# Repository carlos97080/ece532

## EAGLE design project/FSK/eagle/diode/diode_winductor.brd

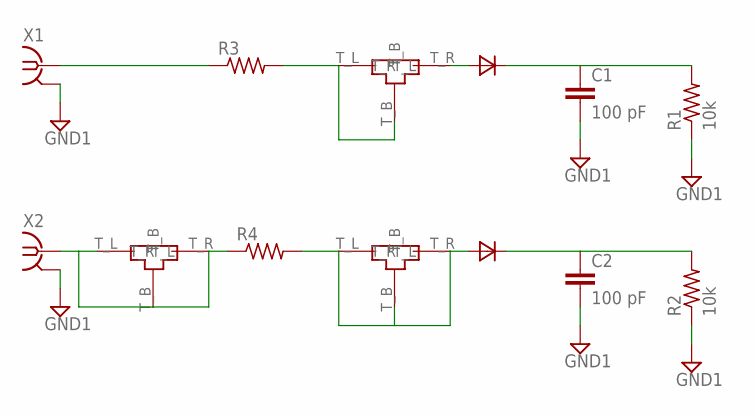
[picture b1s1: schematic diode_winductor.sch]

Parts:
C1, C2: 100 pF; C0603
INPUT, INPUT1, INPUT2: TEE_TL1
R1, R2: 10k; M1206
R3, R4: R-US_R0603; R0603
U$1, U$2: HSMS-2850
X1, X2: SMA-142-0701-801/806; J502-ND-142-0701-801/806

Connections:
GND1: C1.2, C2.2, R1.1, R2.1, X1.G@1 (2), X1.G@2 (2), X1.G@3 (2), X1.G@4 (2), X2.G@1 (2), X2.G@2 (2), X2.G@3 (2), X2.G@4 (2)
INPUT: INPUT.T_B, INPUT.T_L, INPUT.T_R, R3.2, U$1.A
INPUT1: INPUT2.T_B, INPUT2.T_L, INPUT2.T_R, R4.1, X2.1
INPUT2: INPUT1.T_B, INPUT1.T_L, INPUT1.T_R, R4.2, U$2.A
INPUT11: R3.1, X1.1
unnamed: C1.1, R1.2, U$1.C
unnamed: C2.1, R2.2, U$2.C

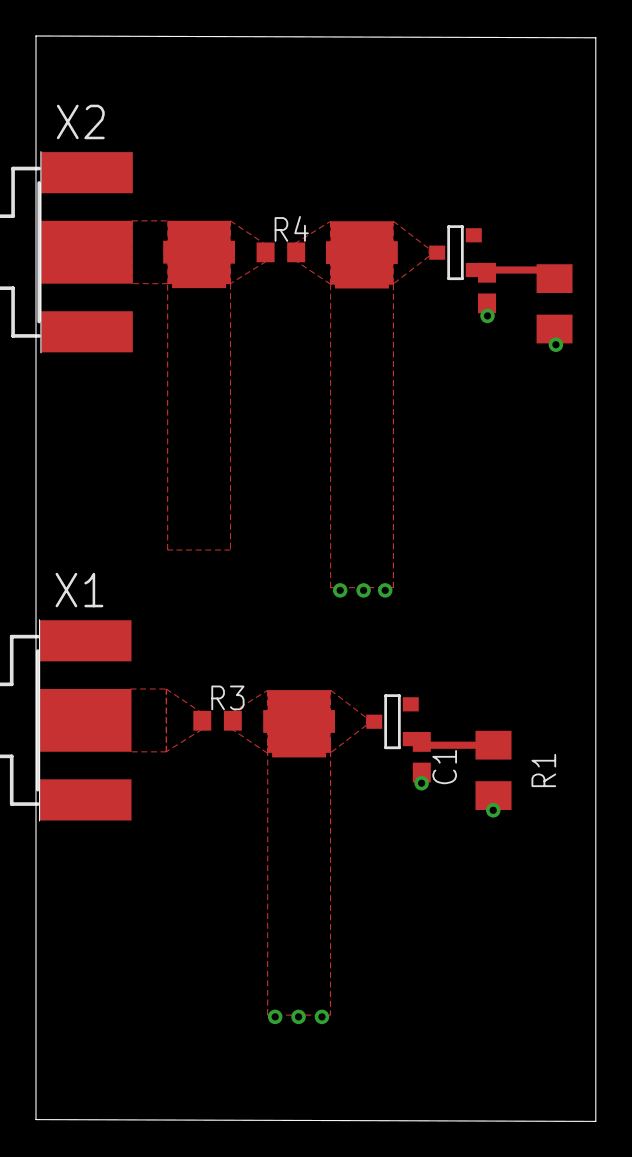
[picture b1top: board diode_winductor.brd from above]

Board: 2 copper layers, 31.1 x 60.3 mm, 13 parts (0 on the bottom side), 7 nets.

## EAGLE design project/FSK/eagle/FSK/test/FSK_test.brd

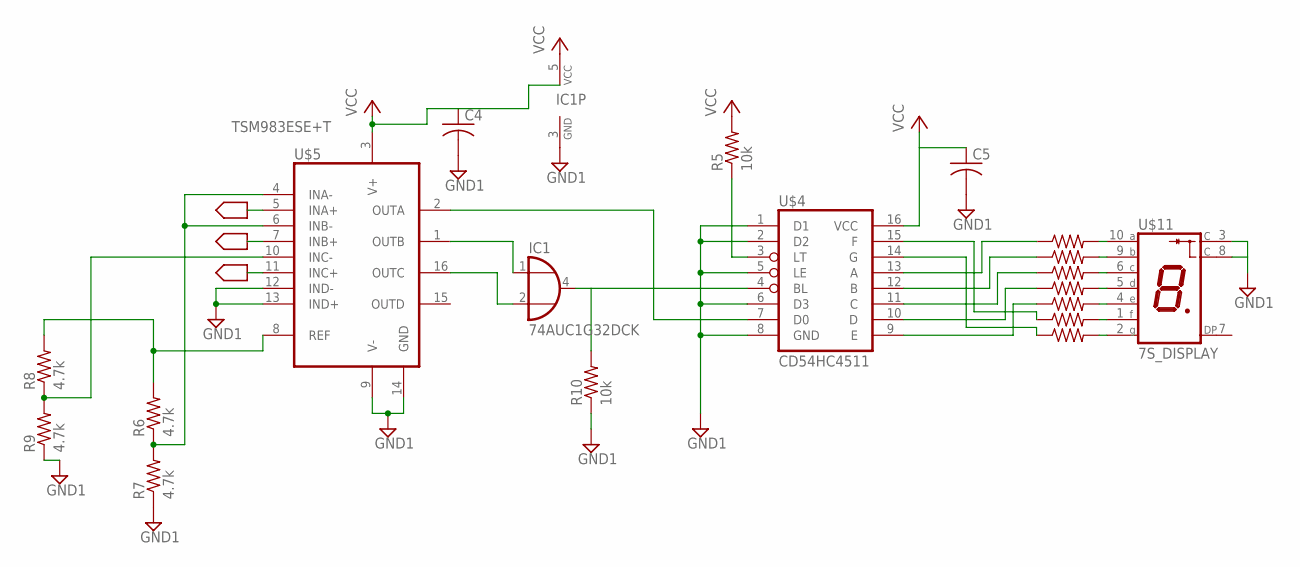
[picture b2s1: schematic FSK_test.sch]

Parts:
C4, C5: C-USC0603; C0603
IC1: 74AUC1G32DCK; SC70-5
R5, R10: 10k; R1206
R6, R7, R8, R9: 4.7k; R1206
R11, R12, R13, R14, R15, R16, R17: R-US_R0603; R0603
U$4: CD54HC4511
U$5: TSM983ESE+T
U$11: 7S_DISPLAY

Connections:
2.4_OUT: U$5.5 (INA+)
2.6_OUT: U$5.7 (INB+), U$5.11 (INC+)
GND1: C4.2, C5.2, IC1.3 (GND), R7.1, R9.1, R10.1, U$4.1 (D1), U$4.2 (D2), U$4.5 (LE), U$4.6 (D3), U$4.8 (GND), U$5.9 (V-), U$5.12 (IND-), U$5.13 (IND+), U$5.14 (GND), U$11.3 (C), U$11.8 (C)
unnamed: IC1.4 (O), R10.2, U$4.4 (BL)
unnamed: IC1.1 (I0), U$5.1 (OUTB)
unnamed: R11.2, U$11.10 (A)
unnamed: R12.2, U$11.9 (B)
unnamed: U$4.7 (D0), U$5.2 (OUTA)
unnamed: R13.2, U$11.6 (C)
unnamed: IC1.2 (I1), U$5.16 (OUTC)
unnamed: R8.1, R9.2, U$5.10 (INC-)
unnamed: R6.2, R8.2, U$5.8 (REF)
unnamed: R6.1, R7.2, U$5.4 (INA-), U$5.6 (INB-)
unnamed: R5.1, U$4.3 (LT)
unnamed: R14.2, U$11.5 (D)
unnamed: R15.2, U$11.4 (E)
unnamed: R16.2, U$11.1 (F)
unnamed: R17.2, U$11.2 (G)
unnamed: R11.1, U$4.13 (A)
unnamed: R12.1, U$4.12 (B)
unnamed: R13.1, U$4.11 (C)
unnamed: R14.1, U$4.10 (D)
unnamed: R15.1, U$4.9 (E)
unnamed: R16.1, U$4.15 (F)
unnamed: R17.1, U$4.14 (G)
VCC: C4.1, C5.1, IC1.5 (VCC), R5.2, U$4.16 (VCC), U$5.3 (V+)

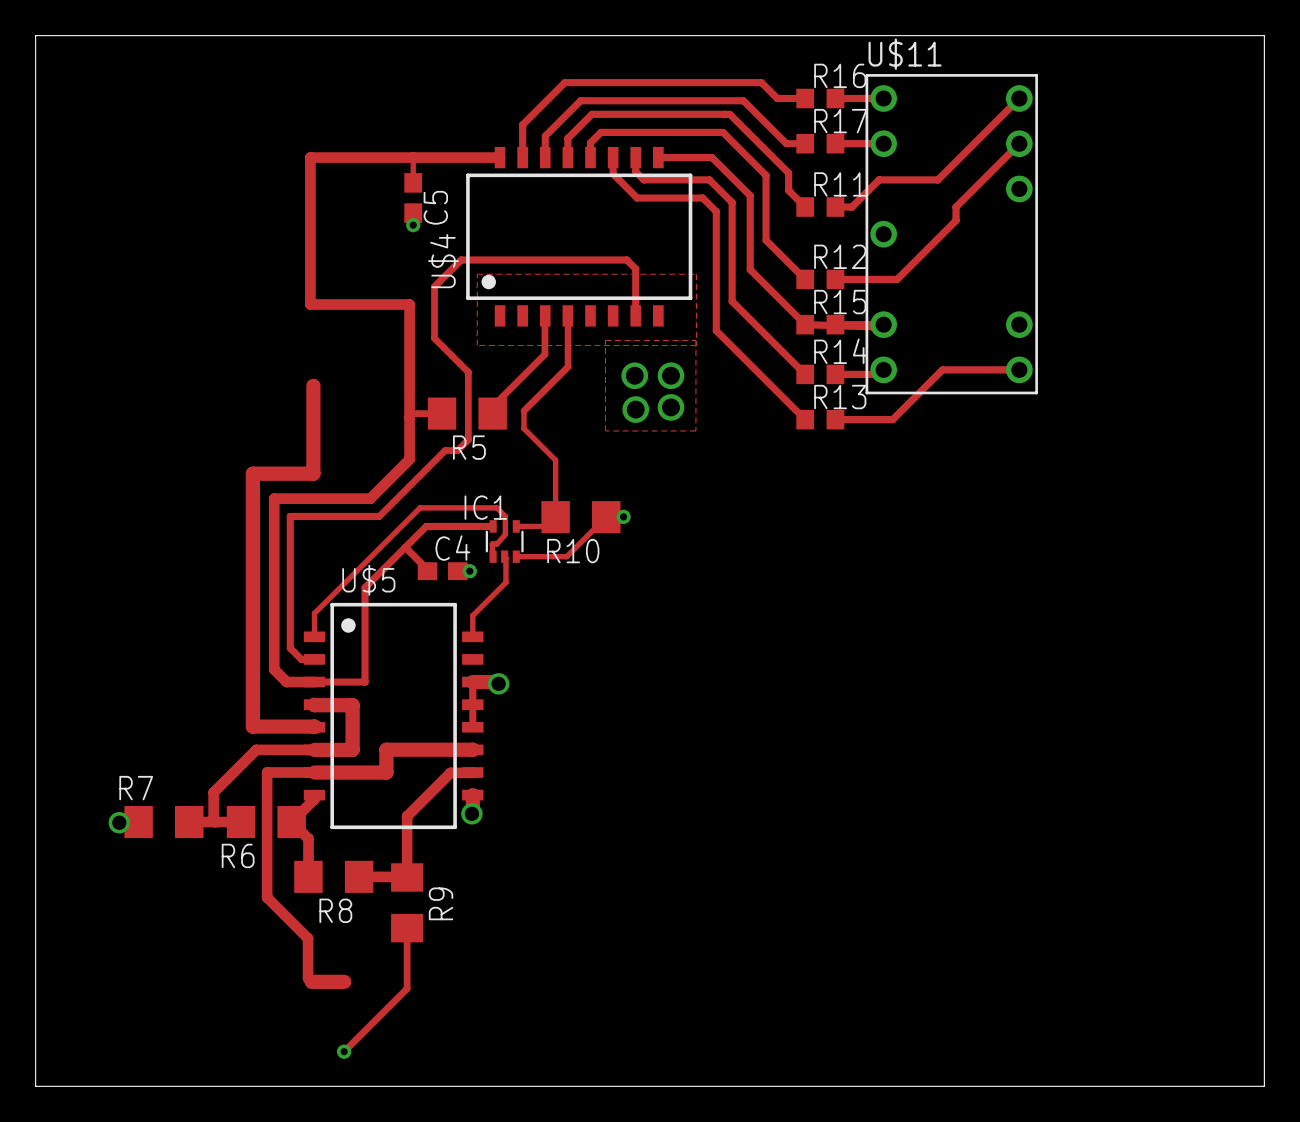
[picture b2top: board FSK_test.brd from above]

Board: 2 copper layers, 69.0 x 59.0 mm, 19 parts (0 on the bottom side), 25 nets.

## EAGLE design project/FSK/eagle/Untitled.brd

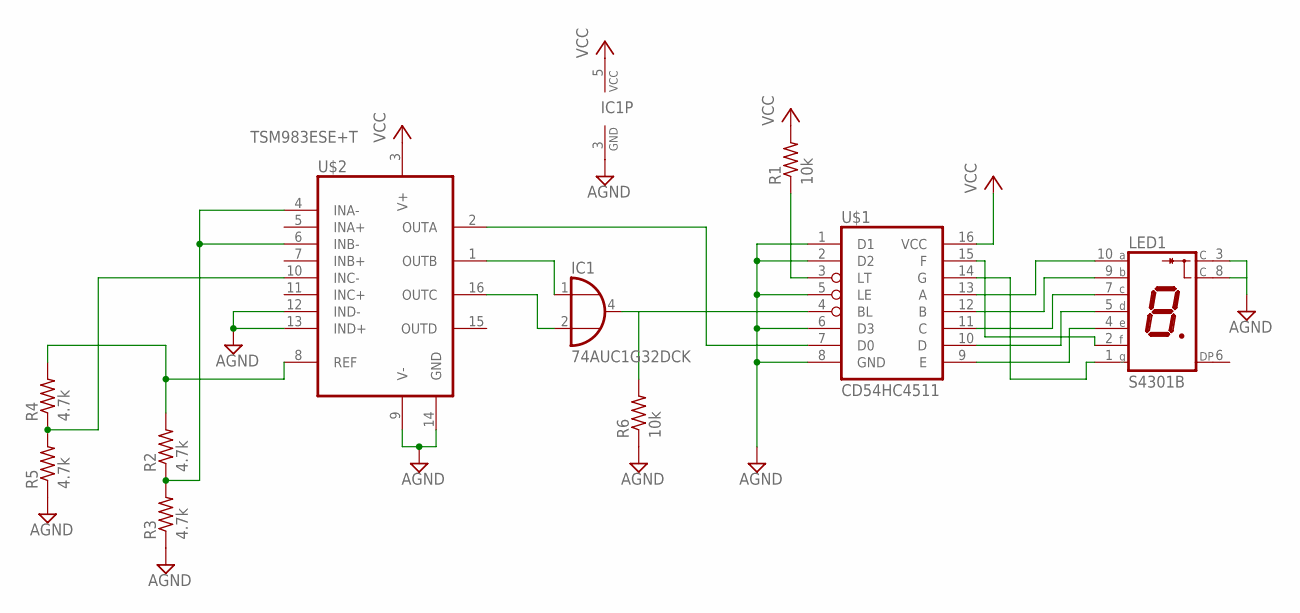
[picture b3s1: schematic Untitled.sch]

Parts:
IC1: 74AUC1G32DCK; SC70-5
LED1: S4301B
R1, R6: 10k; R1206
R2, R3, R4, R5: 4.7k; R1206
U$1: CD54HC4511
U$2: TSM983ESE+T

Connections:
AGND: IC1.3 (GND), LED1.3 (C), LED1.8 (C), R3.1, R5.1, R6.1, U$1.1 (D1), U$1.2 (D2), U$1.5 (LE), U$1.6 (D3), U$1.8 (GND), U$2.9 (V-), U$2.12 (IND-), U$2.13 (IND+), U$2.14 (GND)
unnamed: IC1.1 (I0), U$2.1 (OUTB)
unnamed: R1.1, U$1.3 (LT)
unnamed: IC1.4 (O), R6.2, U$1.4 (BL)
unnamed: IC1.2 (I1), U$2.16 (OUTC)
unnamed: R4.1, R5.2, U$2.10 (INC-)
unnamed: U$1.7 (D0), U$2.2 (OUTA)
unnamed: R2.1, R3.2, U$2.4 (INA-), U$2.6 (INB-)
unnamed: LED1.4 (E), U$1.9 (E)
unnamed: LED1.5 (D), U$1.10 (D)
unnamed: R2.2, R4.2, U$2.8 (REF)
unnamed: LED1.7 (C), U$1.11 (C)
unnamed: LED1.9 (B), U$1.12 (B)
unnamed: LED1.10 (A), U$1.13 (A)
unnamed: LED1.1 (G), U$1.14 (G)
unnamed: LED1.2 (F), U$1.15 (F)
VCC: IC1.5 (VCC), R1.2, U$1.16 (VCC), U$2.3 (V+)

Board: 2 copper layers, 10 parts (0 on the bottom side), 17 nets, no tracks yet.

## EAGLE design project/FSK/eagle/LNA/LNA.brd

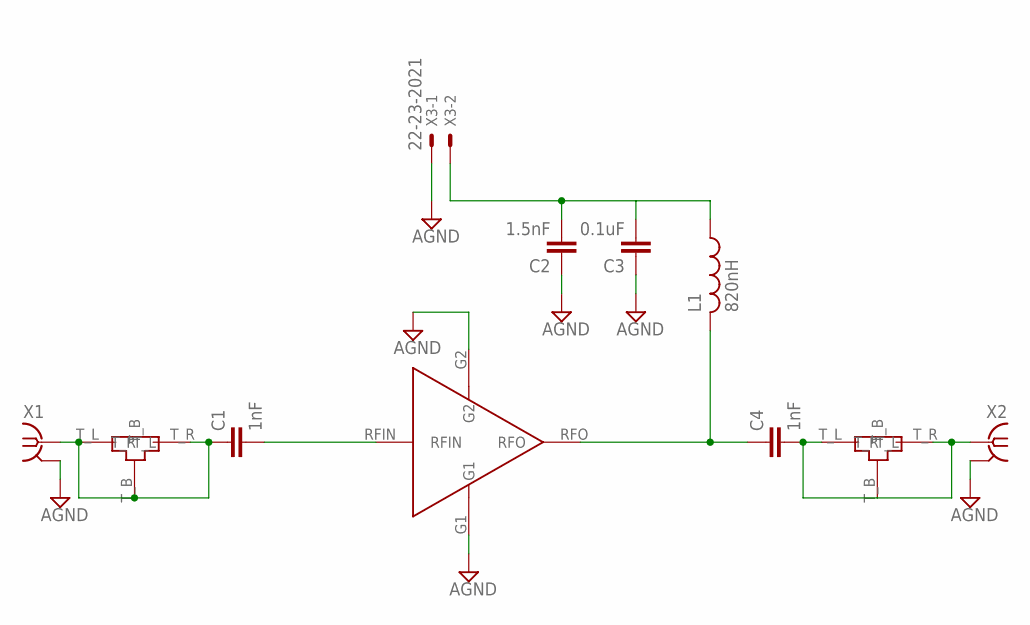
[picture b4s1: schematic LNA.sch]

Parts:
C1, C4: 1nF; C0603
C2: 1.5nF; C0603
C3: 0.1uF; C0603
IN1: TEE_TL1
L1: 820nH; L3230M
OUT2: TEE_TL1
U$1: PSA4-5043+
X1, X2: SMA-142-0711-821/826; J502-ND-142-0711-821/826
X3: 22-23-2021

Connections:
AGND: C2.1, C3.1, U$1.G1, U$1.G2, X1.G@1 (2), X1.G@2 (2), X1.G@3 (2), X1.G@4 (2), X2.G@1 (2), X2.G@2 (2), X2.G@3 (2), X2.G@4 (2), X3.1
EIP: C2.2, C3.2, L1.1, X3.2
IN: C1.2, U$1.RFIN
IN1: C1.1, IN1.T_B, IN1.T_L, IN1.T_R, X1.1
OUT: C4.1, L1.2, U$1.RFO
OUT2: C4.2, OUT2.T_B, OUT2.T_L, OUT2.T_R, X2.1

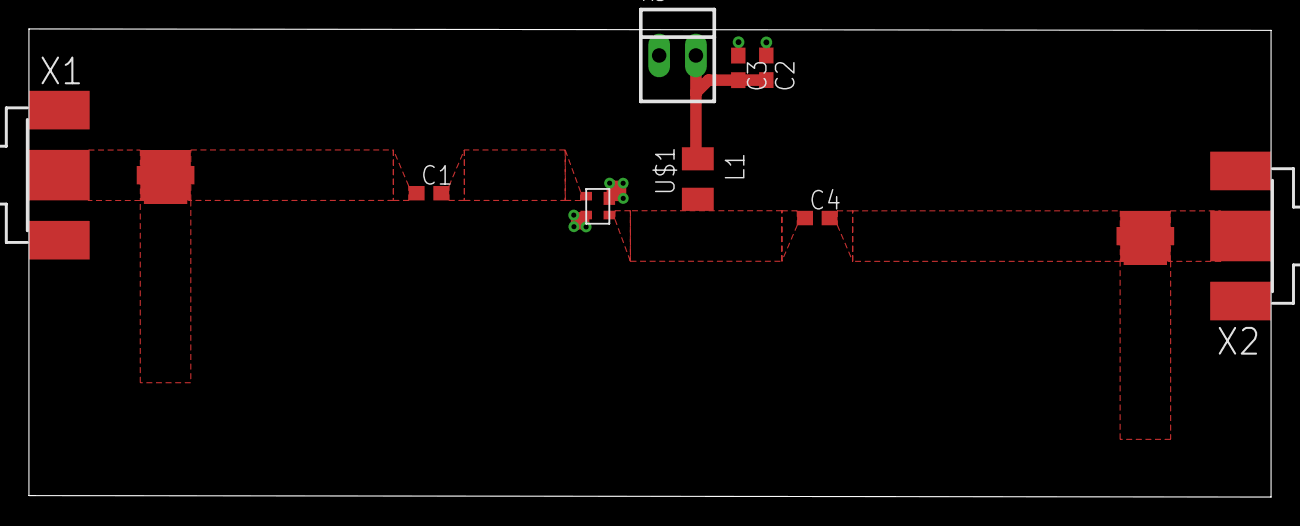
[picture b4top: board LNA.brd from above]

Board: 2 copper layers, 85.8 x 32.4 mm, 11 parts (0 on the bottom side), 6 nets.

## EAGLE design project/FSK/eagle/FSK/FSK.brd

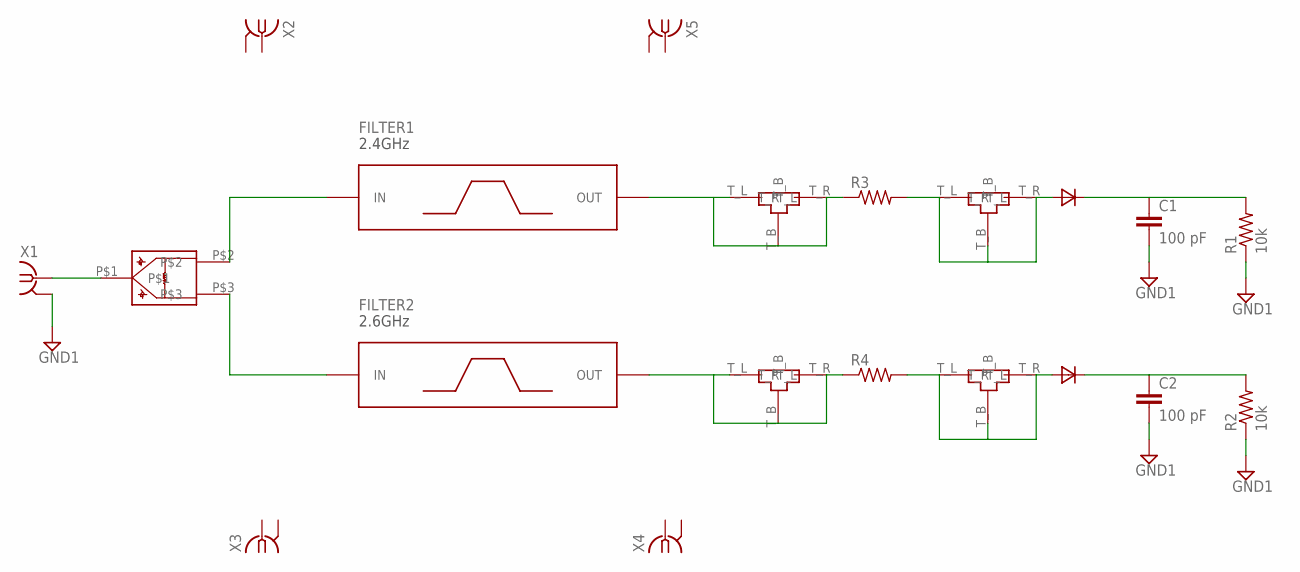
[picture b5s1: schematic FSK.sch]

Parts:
2.4FIL, 2.4TUNED, 2.6FIL, 2.6TUNED: TEE_TL1
C1, C2: 100 pF; C0603
FILTER1: 2.4GHz; 1IN_PIPE_CAP
FILTER2: 2.6GHz; 1IN_PIPE_CAP
R1, R2: 10k; M1206
R3, R4: R-US_R0603; R0603
U$1: WSPLITTER_2.5GHZ
U$2, U$3: HSMS-2850
X1, X2, X3, X4, X5: SMA-142-0711-821/826; J502-ND-142-0711-821/826

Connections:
2.4FIL: 2.4FIL.T_B, 2.4FIL.T_L, 2.4FIL.T_R, FILTER1.OUT, R3.1
2.4GHZ: FILTER1.IN, U$1.P$2
2.4TUNED: 2.4TUNED.T_B, 2.4TUNED.T_L, 2.4TUNED.T_R, R3.2, U$2.A
2.6FIL: 2.6FIL.T_B, 2.6FIL.T_L, 2.6FIL.T_R, FILTER2.OUT, R4.1
2.6GHZ: FILTER2.IN, U$1.P$3
2.6TUNED: 2.6TUNED.T_B, 2.6TUNED.T_L, 2.6TUNED.T_R, R4.2, U$3.A
GND1: C1.2, C2.2, R1.1, R2.1, X1.G@1 (2), X1.G@2 (2), X1.G@3 (2), X1.G@4 (2)
unnamed: C1.1, R1.2, U$2.C
unnamed: C2.1, R2.2, U$3.C
unnamed: U$1.P$1, X1.1

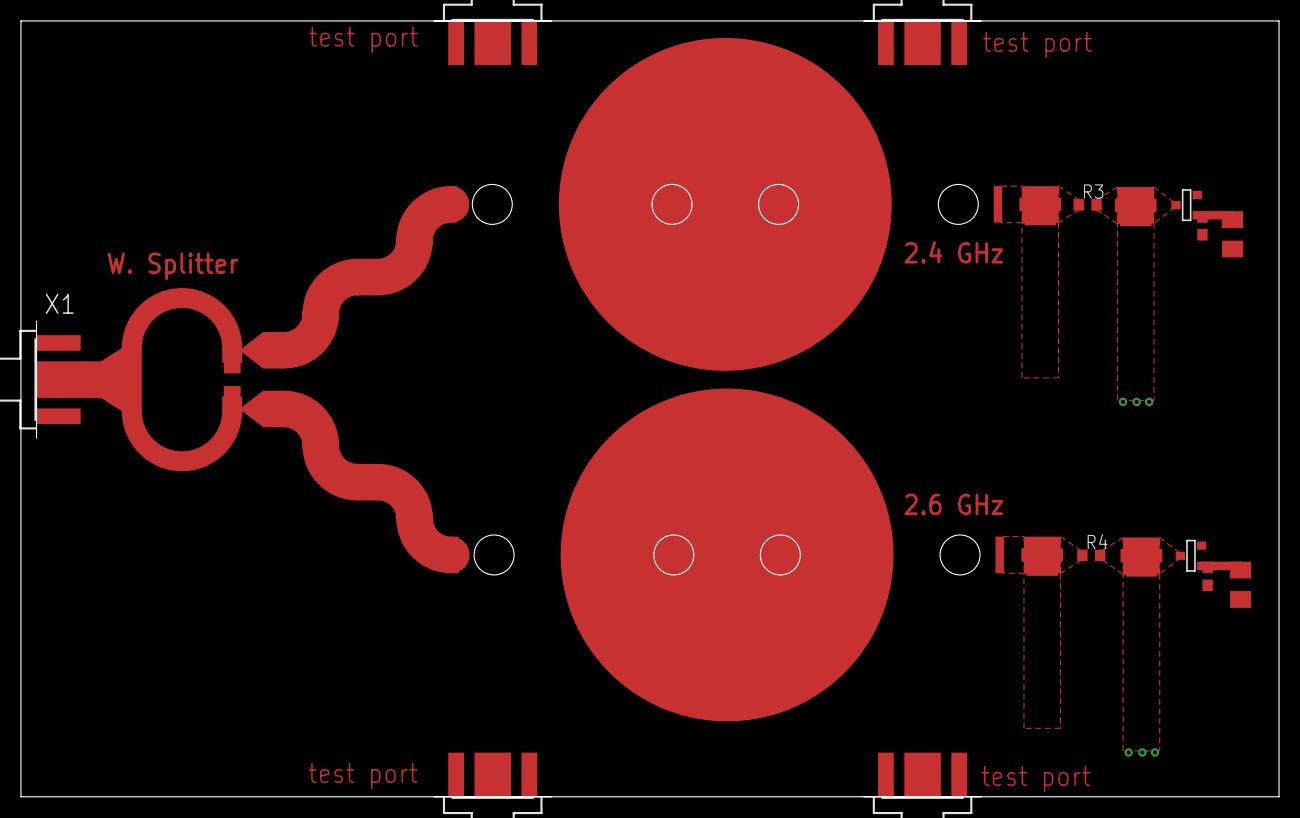
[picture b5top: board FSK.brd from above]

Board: 2 copper layers, 120.0 x 74.0 mm, 20 parts (0 on the bottom side), 10 nets.

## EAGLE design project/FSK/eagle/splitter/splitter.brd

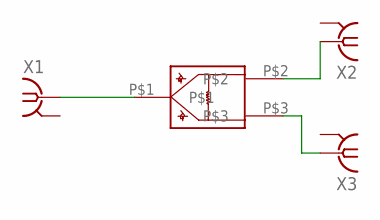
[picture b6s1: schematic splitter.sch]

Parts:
U$1: WSPLITTER_2.5GHZ
X1, X2, X3: SMA-142-0701-801/806; J502-ND-142-0701-801/806

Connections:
IN: U$1.P$1, X1.1
O2: U$1.P$2, X2.1
O3: U$1.P$3, X3.1

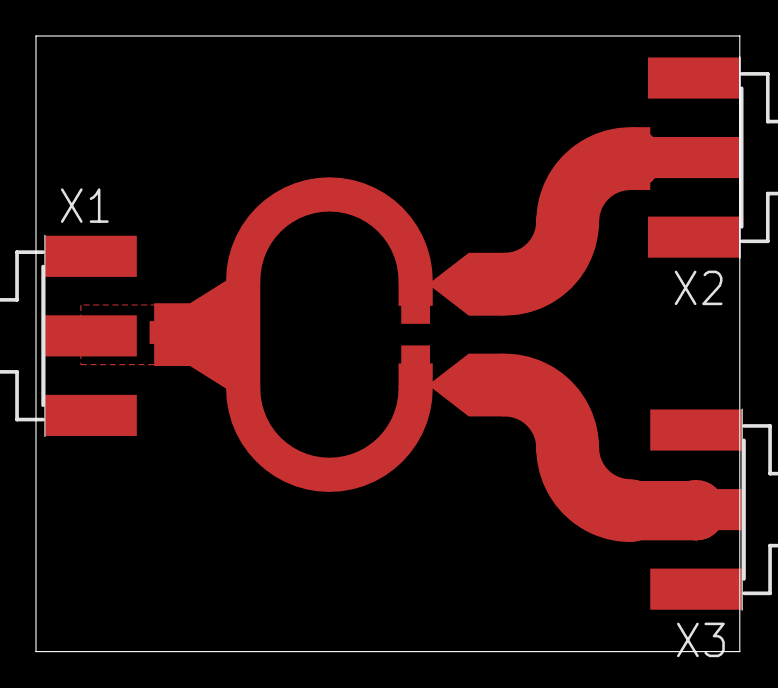
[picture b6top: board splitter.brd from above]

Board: 2 copper layers, 39.2 x 34.2 mm, 4 parts (0 on the bottom side), 3 nets.

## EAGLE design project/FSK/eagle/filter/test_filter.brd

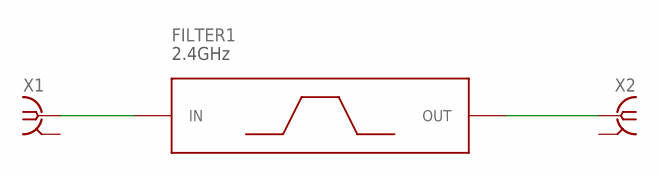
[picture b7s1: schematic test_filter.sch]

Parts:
FILTER1: 2.4GHz; 1IN_PIPE_CAP
X1, X2: SMA-142-0701-801/806; J502-ND-142-0701-801/806

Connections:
IN: FILTER1.IN, X1.1
OUT: FILTER1.OUT, X2.1

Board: 2 copper layers, 3 parts (0 on the bottom side), 2 nets, no tracks yet.

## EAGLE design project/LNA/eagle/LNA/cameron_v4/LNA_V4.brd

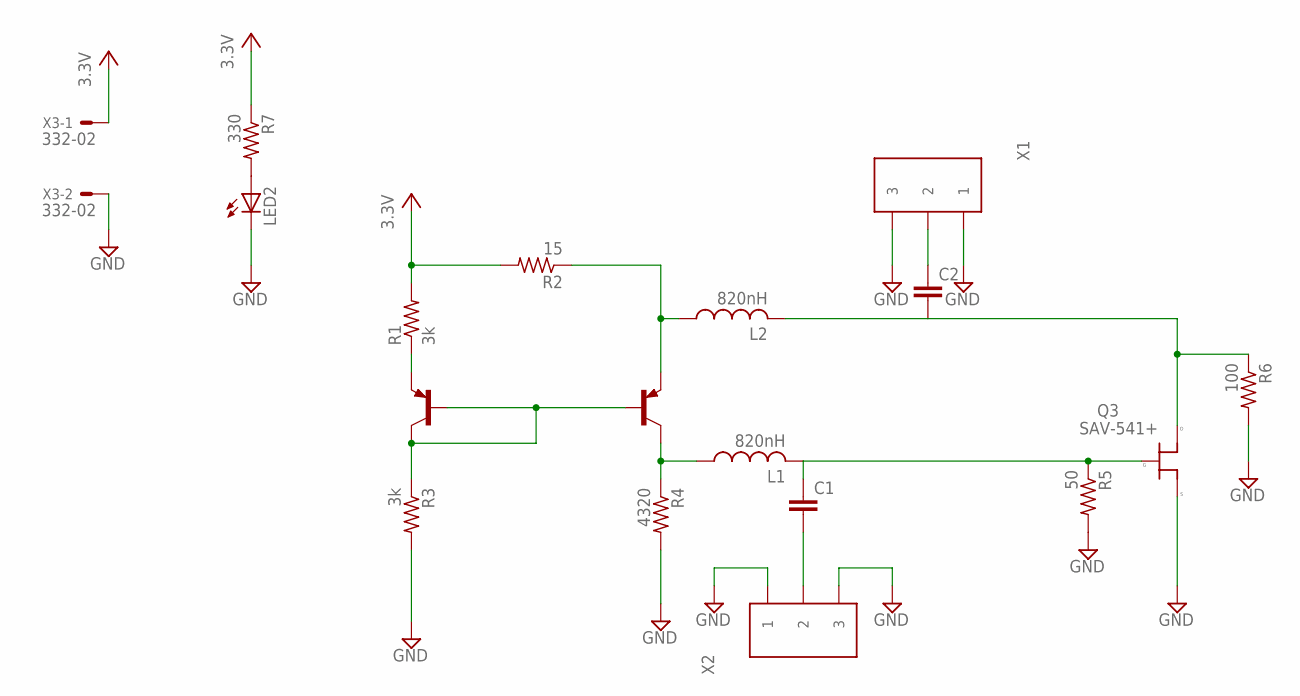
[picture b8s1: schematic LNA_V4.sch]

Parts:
C1, C2: C-EUC0603; C0603
L1, L2: 820nH; L3225M
LED2: LEDCHIPLED_0805; CHIPLED_0805
Q1, Q2: MMBT3906LT1SMD; SOT23-BEC
Q3: SAV-541+; SOT-343
R1, R3: 3k; M0805
R2: 15; M0805
R4: 4320; M0805
R5: 50; M0805
R6: 100; M0805
R7: 330; M0805
X1, X2: PROBE_LANDING
X3: 332-02

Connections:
+3.3V: R1.2, R2.2, R7.1, X3.1
GND: LED2.C, Q3.2 (S), Q3.4 (S), R3.2, R4.2, R5.2, R6.2, X1.1, X1.3, X2.1, X2.3, X3.2
INPUT: C1.1, L1.2, Q3.3 (G), R5.1
ISO_INPUT: C1.2, X2.2
ISO_OUTPUT: C2.1
unnamed: Q1.B, Q1.C, Q2.B, R3.1
unnamed: LED2.A, R7.2
unnamed: Q1.E, R1.1
OUTPUT: C2.2, L2.2, Q3.1 (D), R6.1
VD: L2.1, Q2.E, R2.1
VG: L1.1, Q2.C, R4.1

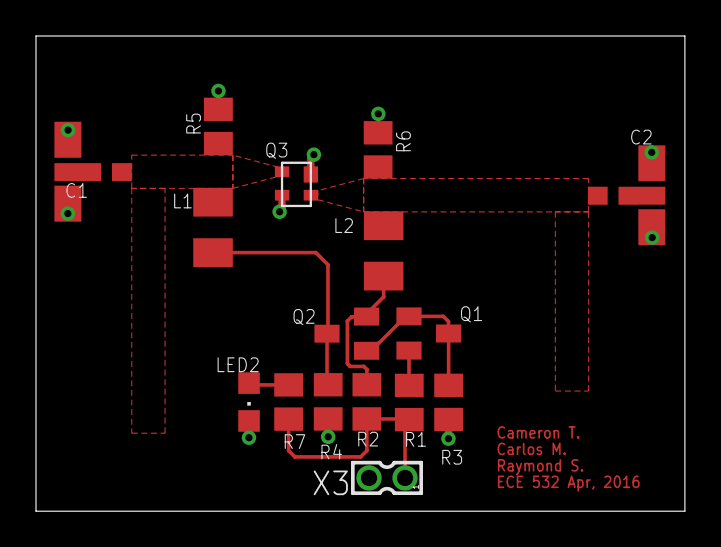
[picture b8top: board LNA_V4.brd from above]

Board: 2 copper layers, 36.0 x 26.4 mm, 18 parts (0 on the bottom side), 10 nets.

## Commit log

2016-04-02 intial commit, added some datasheets and DC bias circuit simulation
2016-04-02 added DC schem (still needs work)
2016-04-02 added sav-541+ to ece532 library
2016-04-02 fixed lbr
2016-04-04 created layout for DC bias circuit
2016-04-04 modified DC board and cleared up directory
    made gerbers too
2016-04-06 added s2p files from mini circuits. added data from Brano (DC characteristics)
2016-04-07 added measured s2p data
2016-04-07 added book
2016-04-07 added second s-parameters from lab
2016-04-10 added workplace for project LNA
2016-04-11 added pdf for HW1
2016-04-11 added LNA schematic for thinner pcb
2016-04-11 created HW1 folder
2016-04-12 added lab 2 pdf
2016-04-12 added workspace for smaller PCB
2016-04-14 created tappered TL
2016-04-15 created schematic and layout for LNA version1
2016-04-15 minor updates to layout, removed some vias
2016-04-15 minor updates to layout, made board smaller
2016-04-19 added edits of lna board
2016-04-19 added lab 2 stuff
2016-04-19 updated lna board
2016-04-19 created resources directory
2016-04-19 added resources and lab3
2016-04-23 added LNA layout with inductors
2016-04-24 created layout for LNa with TL as choke
2016-04-24 small mods to TL choke brd
2016-04-24 simulations for .8mm LNA
2016-04-24 added stabilizing resistors
2016-04-27 Made version 2 of LNA. Added text and corrected footprints
2016-04-27 added berbers
2016-04-27 added measurments from camaronie v1
2016-04-27 added my LNA workspace
2016-04-27 created directory for LNA_V2
2016-04-28 Lab 3 is done, minor changes to LNA PCB
2016-04-28 added libarry for battery holder
2016-04-28 made pdf of report, started TRL calibration PCB
2016-04-29 Added gerbers to V3 LNA
2016-04-29 fixed crooked board outline
2016-04-29 created berbers for TRL cal board
2016-05-03 added measurements for batt wtrl
2016-05-04 added fpc landing pad LNA
2016-05-04 created directory for FSK project and LNA project
2016-05-04 created gerbers for version 4 LNA
2016-05-06 added datasheets for FSK stuff
2016-05-06 added report
2016-05-09 added FSK of splitter
2016-05-09 added splitter gerber
2016-05-10 added splitter and LNA design
2016-05-11 added footprint for pipe cap filter
2016-05-11 added gerbers for test filter board
2016-05-12 updated gerbers
2016-05-12 added V4 LNA measurements
    These have probe landing pads.
2016-05-13 created test board for diode
2016-05-14 moved documentation and created gerbers for packaged lna
2016-05-14 added diode with inductor matching
2016-05-15 changed traces on the LNA board to be 500 ohm, started FSK schematic
2016-05-15 start red FSK board
2016-05-15 finished footprint for pipe cap filter
2016-05-15 routed FSK test board
2016-05-15 fixed FSK board
2016-05-16 updated LNA for the FSK with different tapers
2016-05-16 added more vias to the LNA for lower inductance to gnd
2016-05-16 added gerbers for LNA
2016-05-16 updated gerbers to get rid of extra polygons
2016-05-16 added gervers for FSK
2016-05-17 added the start of the report
2016-05-17 added 7-set data sheet
2016-05-17 added schematic for 7segment driver
2016-05-18 added FSK version 2
2016-05-18 updates to FSK board
2016-05-18 fixed footprints for comp. and SSD driver
2016-05-19 updated gerbers for test board
2016-05-19 added final schem for FSK board and gerbers
2016-05-20 Updated final report
2016-05-20 updated FSK board
2016-05-22 created folder for SLR added my summary and my paper,also a good refecnce paper
2016-05-23 added gitgnore for eagle files
2016-05-24 created SLR report
2016-05-25 worked some more on SLR
2016-05-25 Added my summary for SLR
2016-05-25 updates to SLR and uploaded compression point data
2016-05-25 move camerons paper to papers folder
2016-05-27 repo clean up and updates to FSK report
2016-05-27 updates to SLR added Raymods paper
2016-05-28 added my section of the SLR
2016-06-01 updates to SLR all we need is Rays section
2016-06-01 Continued work on FSK report. Almost done, just need conclusion.
2016-06-01 formatinf and spelling corrected on FSK paper
2016-06-01 added conclusion, just need references
2016-06-02 Finished report conclusion and references
2016-06-02 final report grammar corrections
2016-06-08 corrected axis labels
2016-06-08 Added Raymonds section to the final report
2016-06-17 final report
